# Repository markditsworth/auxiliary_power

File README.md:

# General Purpose Auxiliary Power Supply

Provides 12V, 9V, 5V, 3.3V, and/or 1.8V. Pick-and-place, user re-configurable.

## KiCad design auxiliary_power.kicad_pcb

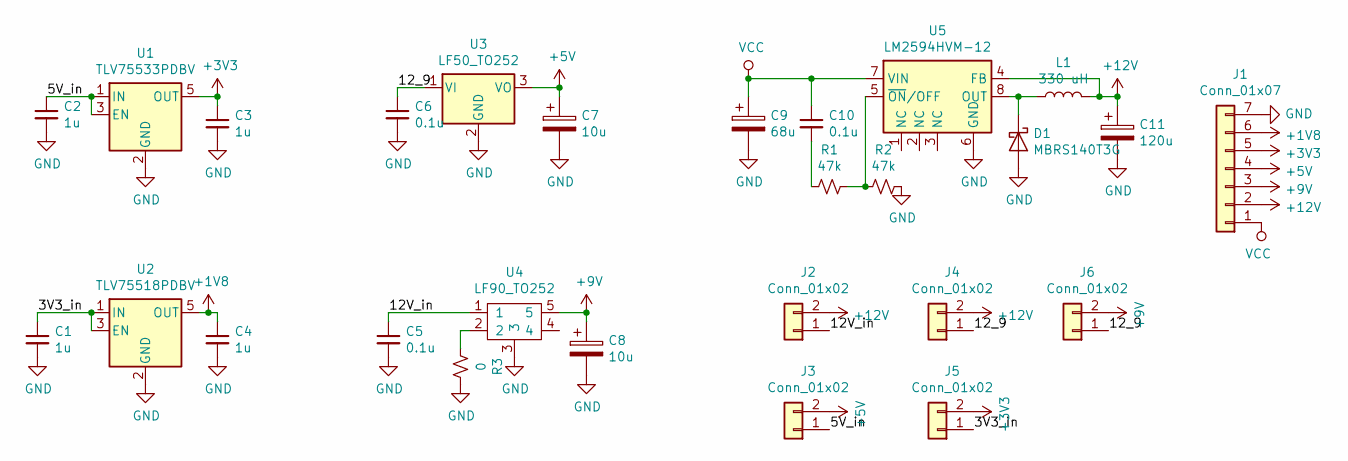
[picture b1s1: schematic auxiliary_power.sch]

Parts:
C1, C2, C3, C4: 1u; C_1206_3216Metric
C5, C6, C10: 0.1u; C_1206_3216Metric
C7, C8: 10u; C_Elec_8x6.2
C9: 68u; C_Elec_8x10.2
C11: 120u; C_Elec_10x10.2
D1: MBRS140T3G; D_SMB_Handsoldering
J1: Conn_01x07; PinHeader_1x07_P2.54mm_Horizontal
J2, J3, J4, J5, J6: Conn_01x02; PinHeader_1x02_P2.54mm_Vertical
L1: 330 uH; L_Bourns_SRR1260
R1, R2: 47k; R_1206_3216Metric
R3: 0; R_1206_3216Metric
U1: TLV75533PDBV; SOT-23-5
U2: TLV75518PDBV; SOT-23-5
U3: LF50_TO252; TO-252-2
U4: LF90_TO252; TO-252-4
U5: LM2594HVM-12; SOIC-8_3.9x4.9mm_P1.27mm

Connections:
+1V8: C4.1, J1.6, U2.5 (OUT)
+3V3: C3.1, J1.5, J5.2, U1.5 (OUT)
+5V: C7.1, J1.4, J3.2, U3.3 (VO)
+9V: C8.1, J1.3, J6.2, U4.5
+12V: C11.1, J1.2, J2.2, J4.2, L1.2, U5.4 (FB)
/3V3_in: C1.1, J5.1, U2.1 (IN), U2.3 (EN)
/5V_in: C2.1, J3.1, U1.1 (IN), U1.3 (EN)
/12V_in: C5.1, J2.1, U4.1
/12_9: C6.1, J4.1, J6.1, U3.1 (VI)
GND: C1.2, C2.2, C3.2, C4.2, C5.2, C6.2, C7.2, C8.2, C9.2, C11.2, D1.2 (A), J1.7, R2.1, R3.1, U1.2 (GND), U2.2 (GND), U3.2 (GND), U4.3, U5.6 (GND)
unnamed: C10.2, R1.2
unnamed: D1.1 (K), L1.1, U5.8 (OUT)
unnamed: R1.1, R2.2, U5.5 (~ON~/OFF)
unnamed: R3.2, U4.2
VCC: C9.1, C10.1, J1.1, U5.7 (VIN)

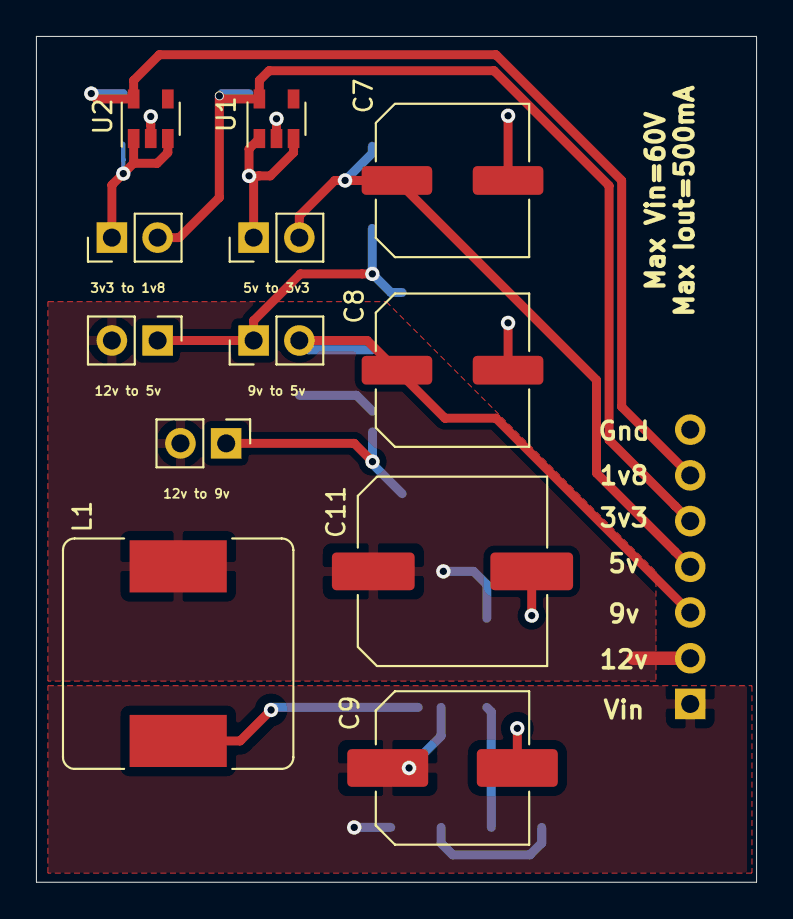
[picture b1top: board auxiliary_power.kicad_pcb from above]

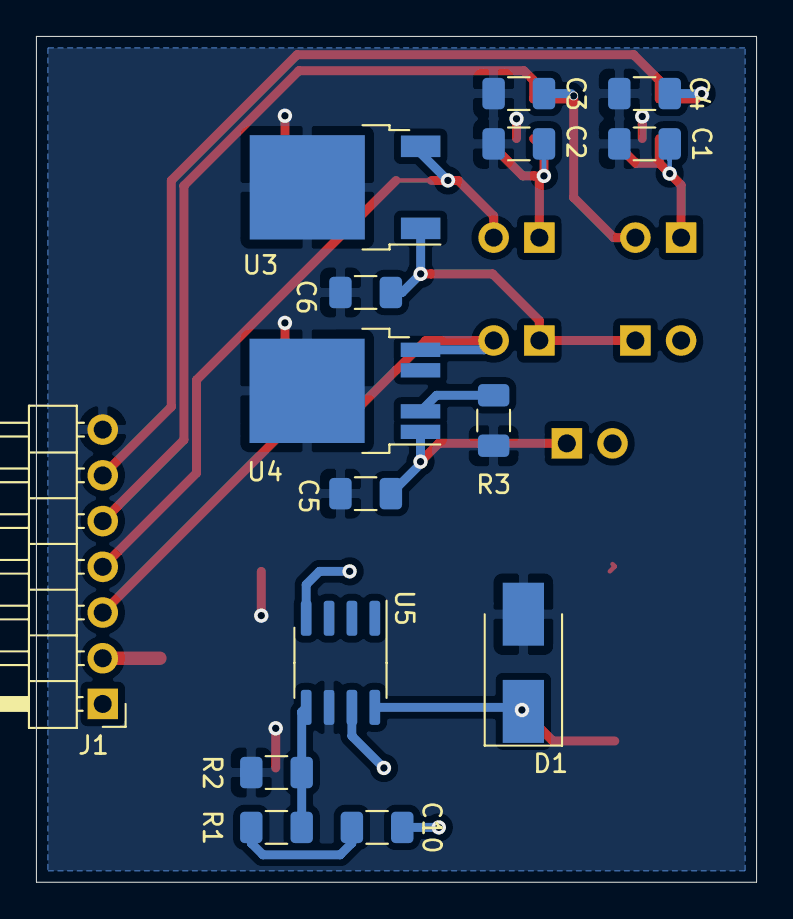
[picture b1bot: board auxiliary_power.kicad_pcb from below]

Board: 2 copper layers, 40.0 x 47.0 mm, 27 parts (15 on the bottom side), 15 nets.
